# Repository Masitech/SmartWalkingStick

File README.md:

# SmartWalkingStick
Arduino ESP8266 based project to detect distance of object and alert it wireless to a bracelet that will vibrate and make sound

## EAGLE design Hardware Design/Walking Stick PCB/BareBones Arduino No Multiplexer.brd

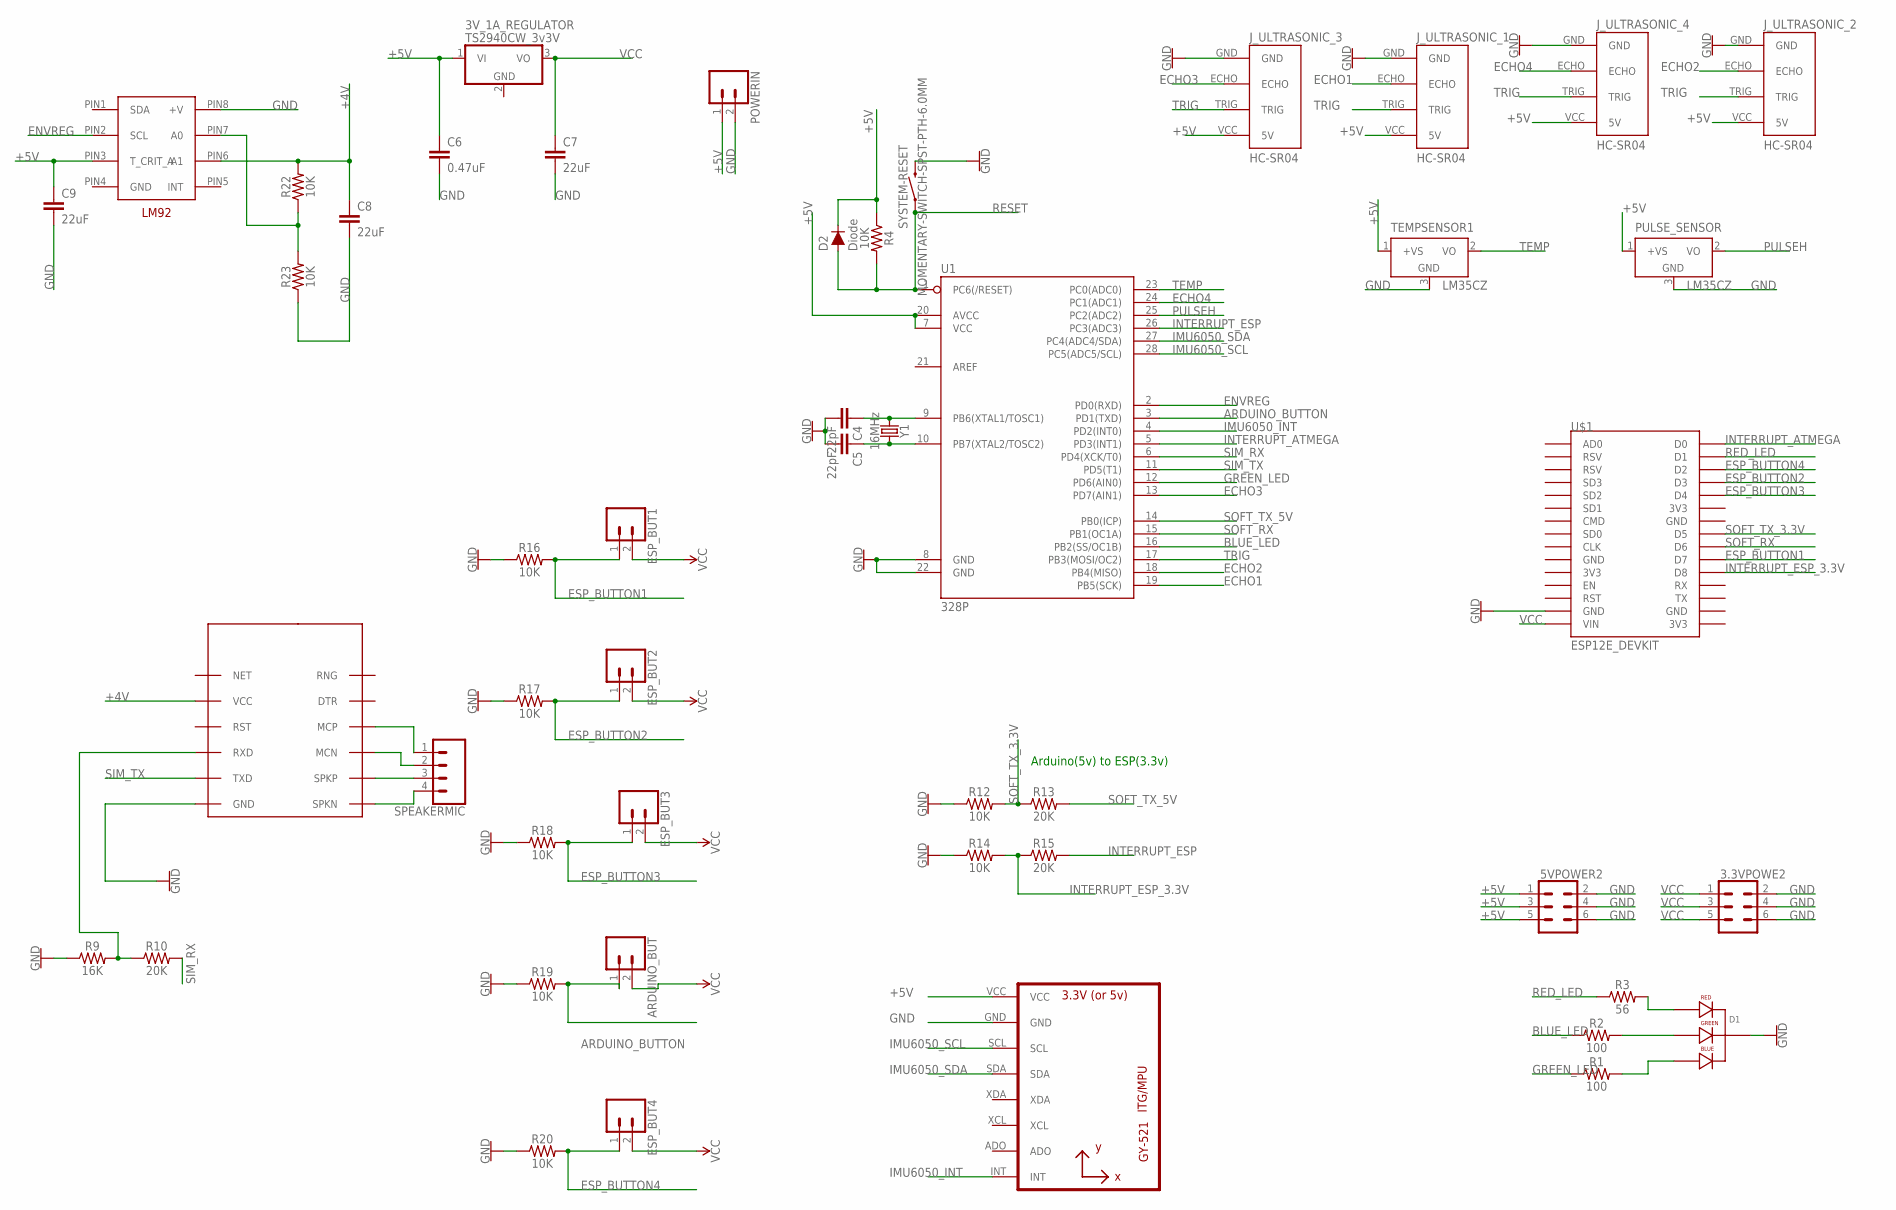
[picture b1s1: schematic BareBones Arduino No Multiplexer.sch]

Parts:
3.3VPOWE2, 5VPOWER2: CONN_03X2FEMALE; 2X3
3V_1A_REGULATOR: TS2940CW_3v3V; SOT223
ARDUINO_BUT: CONN_02; 1X02
C4, C5: 22pF; CAP-PTH-2.54
C6: 0.47uF; CAP-PTH-SMALL-KIT
C7, C8, C9: 22uF; CAP-PTH-SMALL-KIT
D1: LED-RGB-CC-THRUDIFFUSE; LED-RGB-THRU
D2: Diode; DIODE-1N4148
ESP_BUT1, ESP_BUT2, ESP_BUT3, ESP_BUT4: CONN_02; 1X02
J_ULTRASONIC_1, J_ULTRASONIC_2, J_ULTRASONIC_3, J_ULTRASONIC_4: HC-SR04; HC-SR04_FOOTPRINT
POWERIN: CONN_025MM; SCREWTERMINAL-5MM-2
PULSE_SENSOR: LM35CZ; TO92
R1, R2: 100; AXIAL-0.3
R3: 56; AXIAL-0.3
R4, R12, R14, R16, R17, R18, R19, R20, R22, R23: 10K; AXIAL-0.3
R9: 16K; AXIAL-0.3
R10, R13, R15: 20K; AXIAL-0.3
SPEAKERMIC: CONN_04; 1X04
SYSTEM-RESET: MOMENTARY-SWITCH-SPST-PTH-6.0MM; TACTILE_SWITCH_PTH_6.0MM
TEMPSENSOR1: LM35CZ; TO92
U1: 328P; DIP28
U2: GY-521MPU6050; GY-521
U$1: ESP12E_DEVKIT
U$4: SIM800L; SIM-CORE
VREG: LM92; SOP-8
Y1: 16MHz; HC49US

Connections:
+4V: C8.1, R22.P$2 (2), U$4.VCC, VREG.PIN6 (A1)
+5V: 3V_1A_REGULATOR.1 (VI), 5VPOWER2.1, 5VPOWER2.3, 5VPOWER2.5, C6.1, C9.1, D2.C, J_ULTRASONIC_1.VCC (5V), J_ULTRASONIC_2.VCC (5V), J_ULTRASONIC_3.VCC (5V), J_ULTRASONIC_4.VCC (5V), POWERIN.1, PULSE_SENSOR.1 (+VS), R4.P$1 (1), TEMPSENSOR1.1 (+VS), U1.7 (VCC), U1.20 (AVCC), U2.VCC, VREG.PIN3 (T_CRIT_A)
ARDUINO_BUTTON: ARDUINO_BUT.1, R19.P$2 (2), U1.3 (PD1(TXD))
BLUE_LED: R2.P$1 (1), U1.16 (PB2(SS/OC1B))
ECHO1: J_ULTRASONIC_1.ECHO, U1.19 (PB5(SCK))
ECHO2: J_ULTRASONIC_2.ECHO, U1.18 (PB4(MISO))
ECHO3: J_ULTRASONIC_3.ECHO, U1.13 (PD7(AIN1))
ECHO4: J_ULTRASONIC_4.ECHO, U1.24 (PC1(ADC1))
ENVREG: U1.2 (PD0(RXD)), VREG.PIN2 (SCL)
ESP_BUTTON1: ESP_BUT1.1, R16.P$2 (2), U$1.D7
ESP_BUTTON2: ESP_BUT2.1, R17.P$2 (2), U$1.D3
ESP_BUTTON3: ESP_BUT3.1, R18.P$2 (2), U$1.D4
ESP_BUTTON4: ESP_BUT4.1, R20.P$2 (2), U$1.D2
GND: 3.3VPOWE2.2, 3.3VPOWE2.4, 3.3VPOWE2.6, 5VPOWER2.2, 5VPOWER2.4, 5VPOWER2.6, C4.2, C5.2, C6.2, C7.2, C8.2, C9.2, D1.2 (CATHODE), J_ULTRASONIC_1.GND, J_ULTRASONIC_2.GND, J_ULTRASONIC_3.GND, J_ULTRASONIC_4.GND, POWERIN.2, PULSE_SENSOR.3 (GND), R9.P$1 (1), R12.P$1 (1), R14.P$1 (1), R16.P$1 (1), R17.P$1 (1), R18.P$1 (1), R19.P$1 (1), R20.P$1 (1), R23.P$1 (1), SYSTEM-RESET.3 (2), TEMPSENSOR1.3 (GND), U1.8 (GND), U1.22 (GND), U2.GND, U$1.GND@1 (GND), U$4.GND, VREG.PIN8 (+V)
GREEN_LED: R1.P$1 (1), U1.12 (PD6(AIN0))
IMU6050_INT: U1.4 (PD2(INT0)), U2.INT
IMU6050_SCL: U1.28 (PC5(ADC5/SCL)), U2.SCL
IMU6050_SDA: U1.27 (PC4(ADC4/SDA)), U2.SDA
INTERRUPT_ATMEGA: U1.5 (PD3(INT1)), U$1.D0
INTERRUPT_ESP: R15.P$2 (2), U1.26 (PC3(ADC3))
INTERRUPT_ESP_3.3V: R14.P$2 (2), R15.P$1 (1), U$1.D8
unnamed: C5.1, U1.10 (PB7(XTAL2/TOSC2)), Y1.2
unnamed: D1.1 (RED_CATHODE), R3.P$2 (2)
unnamed: D1.3 (GREEN_CATHODE), R2.P$2 (2)
unnamed: D1.4 (BLUE_CATHODE), R1.P$2 (2)
unnamed: SPEAKERMIC.1, U$4.MCP
unnamed: SPEAKERMIC.2, U$4.MCN
unnamed: C4.1, U1.9 (PB6(XTAL1/TOSC1)), Y1.1
unnamed: SPEAKERMIC.3, U$4.SPKP
unnamed: SPEAKERMIC.4, U$4.SPKN
unnamed: R9.P$2 (2), R10.P$1 (1), U$4.RXD
unnamed: R22.P$1 (1), R23.P$2 (2), VREG.PIN7 (A0)
PULSEH: PULSE_SENSOR.2 (VO), U1.25 (PC2(ADC2))
RED_LED: R3.P$1 (1), U$1.D1
RESET: D2.A, R4.P$2 (2), SYSTEM-RESET.1, U1.1 (PC6(/RESET))
SIM_RX: R10.P$2 (2), U1.6 (PD4(XCK/T0))
SIM_TX: U1.11 (PD5(T1)), U$4.TXD
SOFT_RX: U1.15 (PB1(OC1A)), U$1.D6
SOFT_TX_3.3V: R12.P$2 (2), R13.P$1 (1), U$1.D5
SOFT_TX_5V: R13.P$2 (2), U1.14 (PB0(ICP))
TEMP: TEMPSENSOR1.2 (VO), U1.23 (PC0(ADC0))
TRIG: J_ULTRASONIC_1.TRIG, J_ULTRASONIC_2.TRIG, J_ULTRASONIC_3.TRIG, J_ULTRASONIC_4.TRIG, U1.17 (PB3(MOSI/OC2))
VCC: 3.3VPOWE2.1, 3.3VPOWE2.3, 3.3VPOWE2.5, 3V_1A_REGULATOR.3 (VO), ARDUINO_BUT.2, C7.1, ESP_BUT1.2, ESP_BUT2.2, ESP_BUT3.2, ESP_BUT4.2, U$1.VIN

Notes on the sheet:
Arduino(5v) to ESP(3.3v)

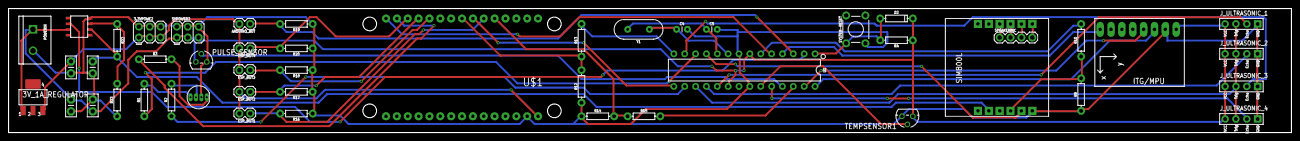
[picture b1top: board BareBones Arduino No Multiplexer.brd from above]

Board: 2 copper layers, 300.0 x 29.0 mm, 48 parts (0 on the bottom side), 43 nets.

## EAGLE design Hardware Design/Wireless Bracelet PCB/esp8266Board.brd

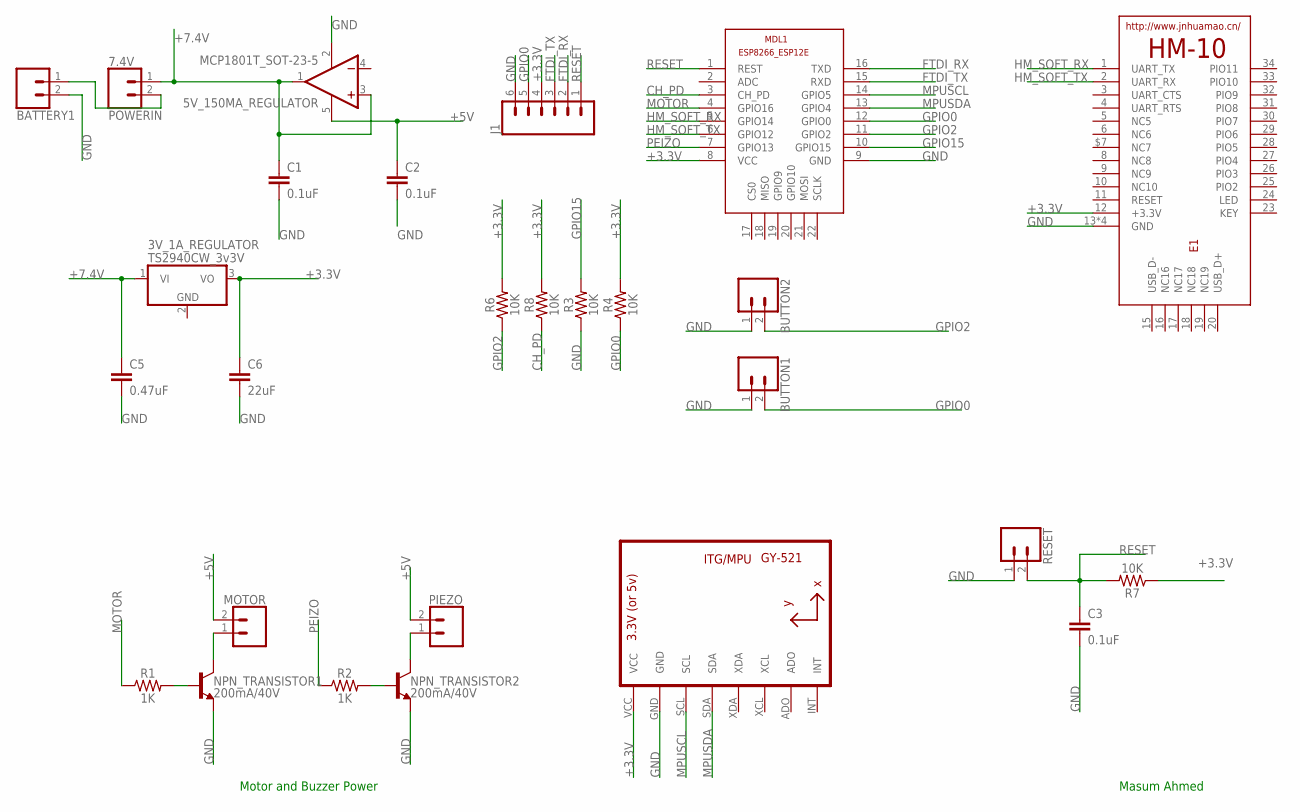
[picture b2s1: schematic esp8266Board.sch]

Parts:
3V_1A_REGULATOR: TS2940CW_3v3V; SOT223
5V_150MA_REGULATOR: MCP1801T_SOT-23-5; SOT23-5
BATTERY1: CONN_02; 1X02
BUTTON1, BUTTON2: CONN_02; 1X02
C1, C2, C3: 0.1uF; 0805
C5: 0.47uF; CAP-PTH-SMALL-KIT
C6: 22uF; CAP-PTH-SMALL-KIT
E1: HM-10-BOARD; 26.9X13X2.2_BOARD
J1: CONN_06SILK_FEMALE_PTH; 1X06
MDL1: ESP8266-12EESP8266-ESP12E; ESP8266-ESP12E
MOTOR: CONN_02; 1X02
NPN_TRANSISTOR1, NPN_TRANSISTOR2: 200mA/40V; TO-92
PIEZO: CONN_02; 1X02
POWERIN: 7.4V; 1X02
R1, R2: 1K; 0805
R3, R4, R6, R7, R8: 10K; 0805
RESET: CONN_02; 1X02
U1: GY-521MPU6050; GY-521

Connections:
+3.3V: 3V_1A_REGULATOR.3 (VO), C6.1, E1.12 (+3.3V), J1.4, MDL1.8 (VCC), R4.2, R6.2, R7.1, R8.2, U1.VCC
+5V: 5V_150MA_REGULATOR.5 (V+), C2.1, MOTOR.2, PIEZO.2
+7.4V: 3V_1A_REGULATOR.1 (VI), 5V_150MA_REGULATOR.1 (OUT), 5V_150MA_REGULATOR.3 (+IN), C1.1, C5.1, POWERIN.1
CH_PD: MDL1.3 (CH_PD), R8.1
FTDI_RX: J1.2, MDL1.16 (TXD)
FTDI_TX: J1.3, MDL1.15 (RXD)
GND: 5V_150MA_REGULATOR.2 (V-), BATTERY1.2, BUTTON1.1, BUTTON2.1, C1.2, C2.2, C3.2, C5.2, C6.2, E1.13 (GND), E1.14 (GND), E1.21 (GND), E1.22 (GND), J1.6, MDL1.9 (GND), NPN_TRANSISTOR1.1 (E), NPN_TRANSISTOR2.1 (E), R3.1, RESET.1, U1.GND
GPIO0: BUTTON1.2, J1.5, MDL1.12 (GPIO0), R4.1
GPIO2: BUTTON2.2, MDL1.11 (GPIO2), R6.1
GPIO15: MDL1.10 (GPIO15), R3.2
HM_SOFT_RX: E1.1 (UART_TX), MDL1.5 (GPIO14)
HM_SOFT_TX: E1.2 (UART_RX), MDL1.6 (GPIO12)
MOTOR: MDL1.4 (GPIO16), R1.1
MPUSCL: MDL1.14 (GPIO5), U1.SCL
MPUSDA: MDL1.13 (GPIO4), U1.SDA
unnamed: BATTERY1.1, POWERIN.2
unnamed: NPN_TRANSISTOR2.2 (B), R2.2
unnamed: NPN_TRANSISTOR1.2 (B), R1.2
unnamed: NPN_TRANSISTOR2.3 (C), PIEZO.1
unnamed: MOTOR.1, NPN_TRANSISTOR1.3 (C)
PEIZO: MDL1.7 (GPIO13), R2.1
RESET: C3.1, J1.1, MDL1.1 (REST), R7.2, RESET.2

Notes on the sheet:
Masum Ahmed
Motor and Buzzer Power

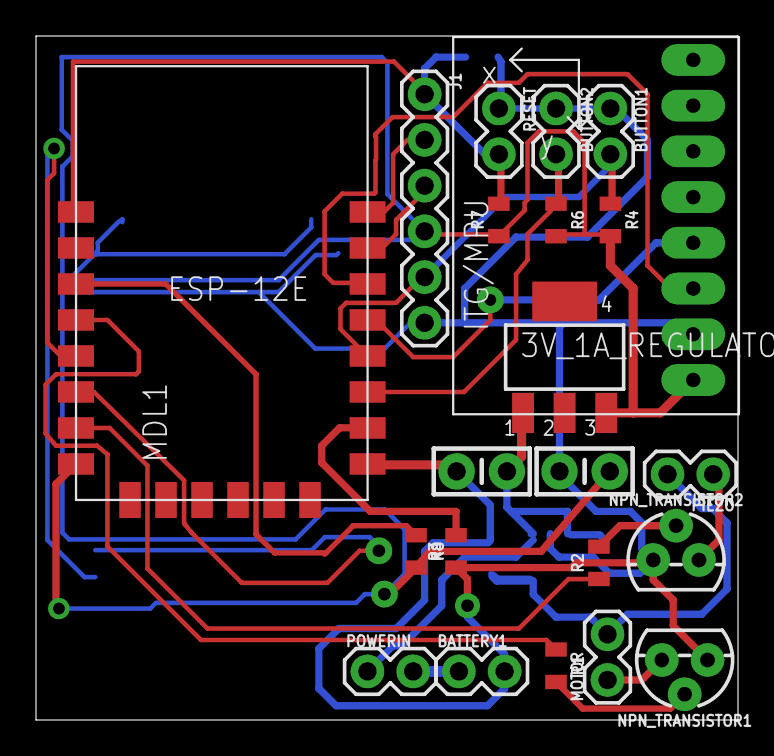
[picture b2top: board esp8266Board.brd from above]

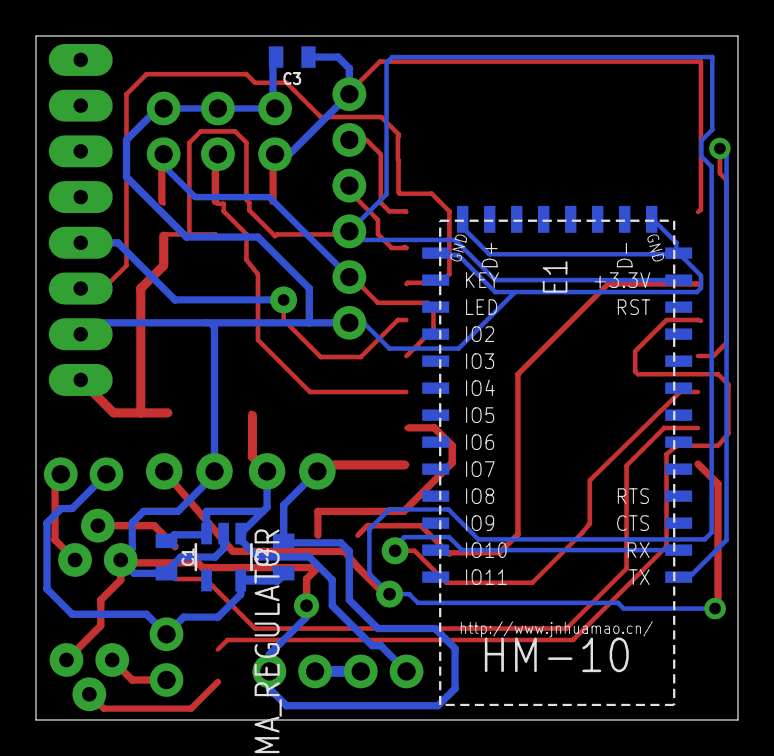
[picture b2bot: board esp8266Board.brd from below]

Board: 2 copper layers, 39.0 x 38.0 mm, 27 parts (5 on the bottom side), 22 nets.

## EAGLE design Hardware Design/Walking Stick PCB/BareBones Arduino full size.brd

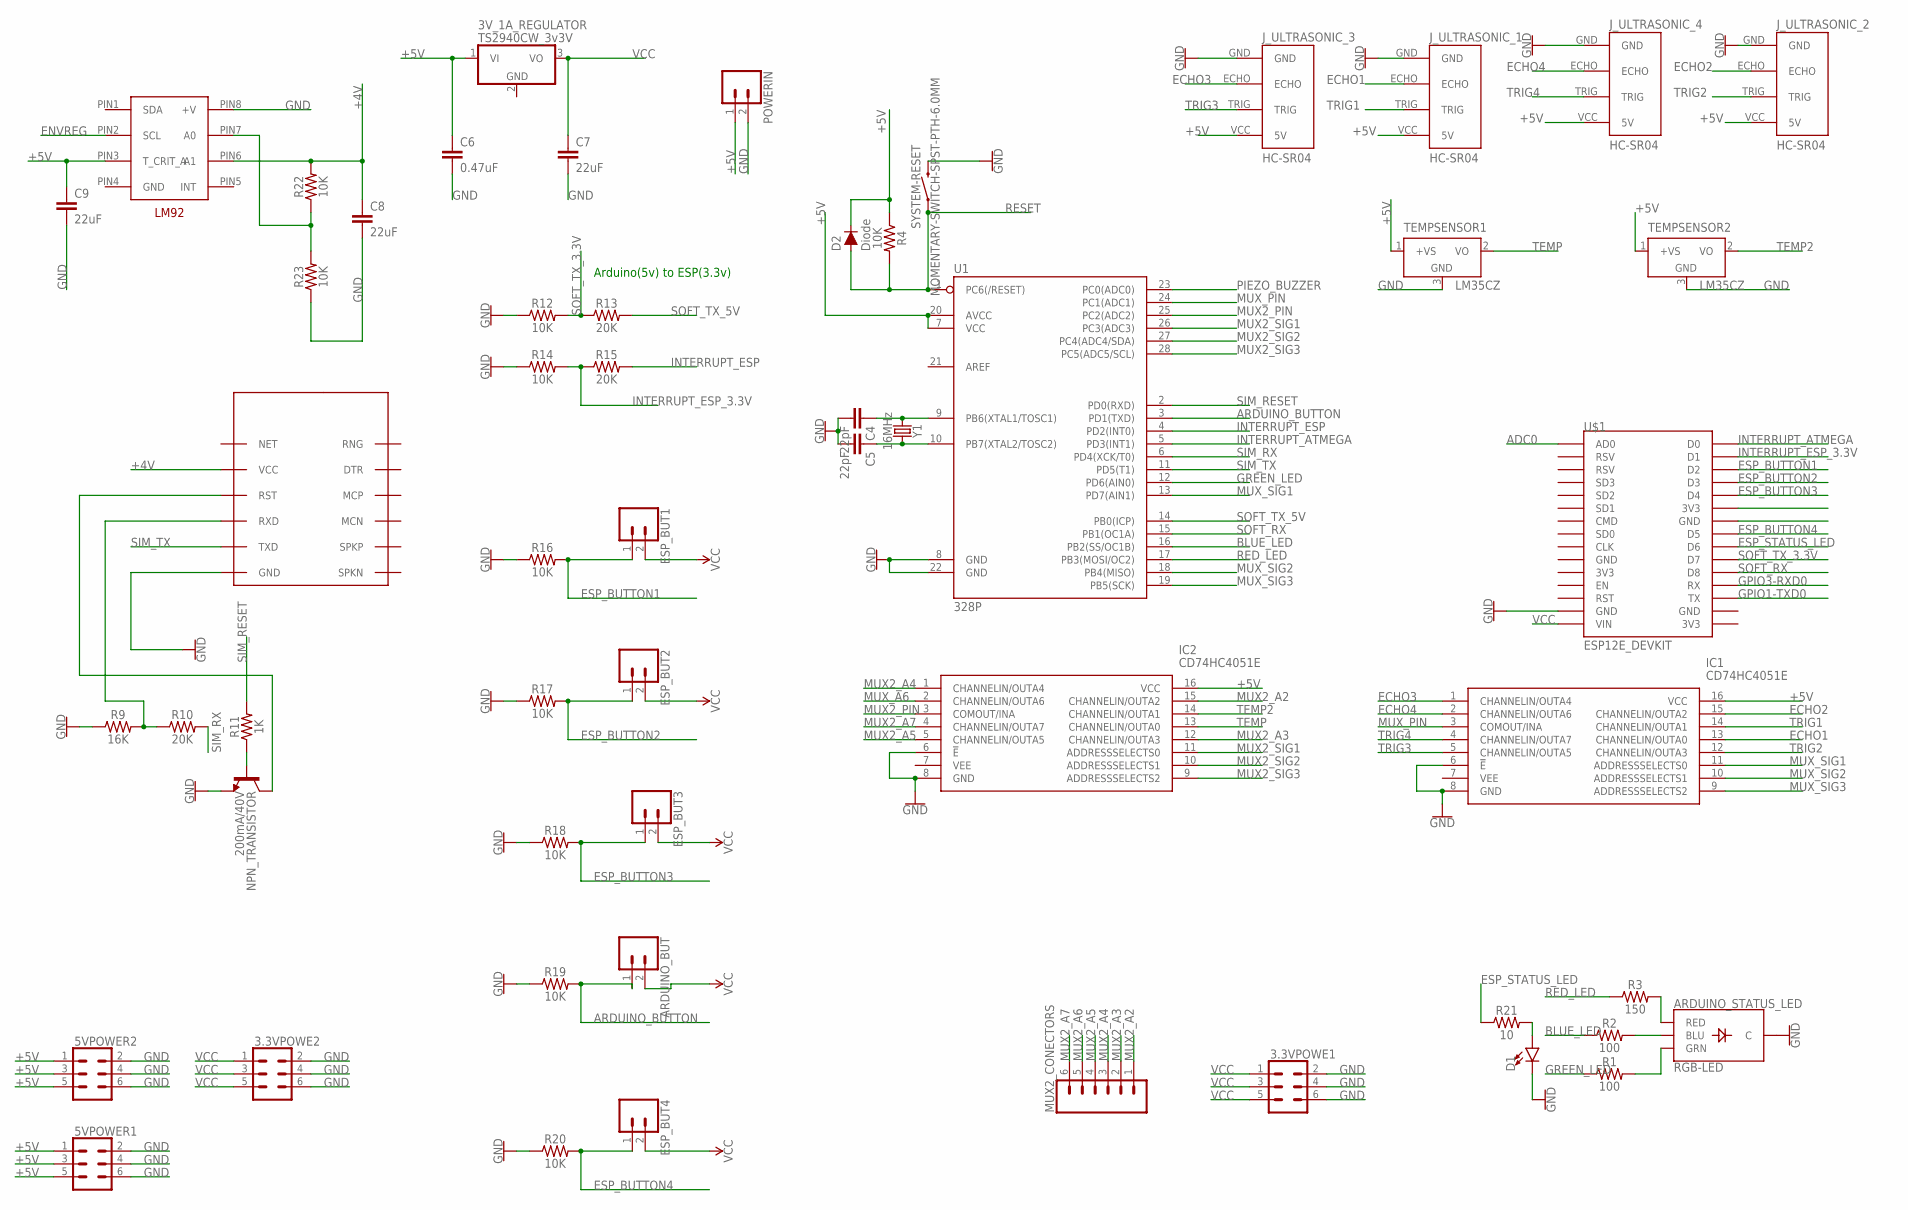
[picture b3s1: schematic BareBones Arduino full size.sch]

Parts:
3.3VPOWE1, 3.3VPOWE2, 5VPOWER1, 5VPOWER2: CONN_03X2FEMALE; 2X3
3V_1A_REGULATOR: TS2940CW_3v3V; SOT223
ARDUINO_BUT: CONN_02; 1X02
ARDUINO_STATUS_LED: RGB-LED; LED-RGB-THRU
C4, C5: 22pF; CAP-PTH-2.54
C6: 0.47uF; CAP-PTH-SMALL-KIT
C7, C8, C9: 22uF; CAP-PTH-SMALL-KIT
D1: LED5MM; LED_5MM
D2: Diode; DIODE-1N4148
ESP_BUT1, ESP_BUT2, ESP_BUT3, ESP_BUT4: CONN_02; 1X02
IC1, IC2: CD74HC4051E; DIP794W53P254L1930H508Q16N
J_ULTRASONIC_1, J_ULTRASONIC_2, J_ULTRASONIC_3, J_ULTRASONIC_4: HC-SR04; HC-SR04_FOOTPRINT
MUX2_CONECTORS: CONN_06SILK_FEMALE_PTH; 1X06
NPN_TRANSISTOR: 200mA/40V; TO-92
POWERIN: CONN_025MM; SCREWTERMINAL-5MM-2
R1, R2: 100; AXIAL-0.3
R3: 150; AXIAL-0.3
R4, R12, R14, R16, R17, R18, R19, R20, R22, R23: 10K; AXIAL-0.3
R9: 16K; AXIAL-0.3
R10, R13, R15: 20K; AXIAL-0.3
R11: 1K; AXIAL-0.3
R21: 10; AXIAL-0.3
SYSTEM-RESET: MOMENTARY-SWITCH-SPST-PTH-6.0MM; TACTILE_SWITCH_PTH_6.0MM
TEMPSENSOR1, TEMPSENSOR2: LM35CZ; TO92
U1: 328P; DIP28
U$1: ESP12E_DEVKIT
U$4: SIM800L; SIM-CORE
VREG: LM92; SOP-8
Y1: 16MHz; HC49US

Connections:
+4V: C8.1, R22.P$2 (2), U$4.VCC, VREG.PIN6 (A1)
+5V: 3V_1A_REGULATOR.1 (VI), 5VPOWER1.1, 5VPOWER1.3, 5VPOWER1.5, 5VPOWER2.1, 5VPOWER2.3, 5VPOWER2.5, C6.1, C9.1, D2.C, IC1.16 (VCC), IC2.16 (VCC), J_ULTRASONIC_1.VCC (5V), J_ULTRASONIC_2.VCC (5V), J_ULTRASONIC_3.VCC (5V), J_ULTRASONIC_4.VCC (5V), POWERIN.1, R4.P$1 (1), TEMPSENSOR1.1 (+VS), TEMPSENSOR2.1 (+VS), U1.7 (VCC), U1.20 (AVCC), VREG.PIN3 (T_CRIT_A)
ADC0: U$1.AD0
ARDUINO_BUTTON: ARDUINO_BUT.1, R19.P$2 (2), U1.3 (PD1(TXD))
BLUE_LED: R2.P$1 (1), U1.16 (PB2(SS/OC1B))
ECHO1: IC1.13 (CHANNELIN/OUTA0), J_ULTRASONIC_1.ECHO
ECHO2: IC1.15 (CHANNELIN/OUTA2), J_ULTRASONIC_2.ECHO
ECHO3: IC1.1 (CHANNELIN/OUTA4), J_ULTRASONIC_3.ECHO
ECHO4: IC1.2 (CHANNELIN/OUTA6), J_ULTRASONIC_4.ECHO
ENVREG: VREG.PIN2 (SCL)
ESP_BUTTON1: ESP_BUT1.1, R16.P$2 (2), U$1.D2
ESP_BUTTON2: ESP_BUT2.1, R17.P$2 (2), U$1.D3
ESP_BUTTON3: ESP_BUT3.1, R18.P$2 (2), U$1.D4
ESP_BUTTON4: ESP_BUT4.1, R20.P$2 (2), U$1.D5
ESP_STATUS_LED: R21.P$1 (1), U$1.D6
GND: 3.3VPOWE1.2, 3.3VPOWE1.4, 3.3VPOWE1.6, 3.3VPOWE2.2, 3.3VPOWE2.4, 3.3VPOWE2.6, 5VPOWER1.2, 5VPOWER1.4, 5VPOWER1.6, 5VPOWER2.2, 5VPOWER2.4, 5VPOWER2.6, ARDUINO_STATUS_LED.2 (C), C4.2, C5.2, C6.2, C7.2, C8.2, C9.2, D1.K (C), IC1.6 (!E), IC1.8 (GND), IC2.6 (!E), IC2.8 (GND), J_ULTRASONIC_1.GND, J_ULTRASONIC_2.GND, J_ULTRASONIC_3.GND, J_ULTRASONIC_4.GND, NPN_TRANSISTOR.1 (E), POWERIN.2, R9.P$1 (1), R12.P$1 (1), R14.P$1 (1), R16.P$1 (1), R17.P$1 (1), R18.P$1 (1), R19.P$1 (1), R20.P$1 (1), R23.P$1 (1), SYSTEM-RESET.3 (2), TEMPSENSOR1.3 (GND), TEMPSENSOR2.3 (GND), U1.8 (GND), U1.22 (GND), U$1.GND@1 (GND), U$4.GND, VREG.PIN8 (+V)
GPIO1-TXD0: U$1.TX
GPIO3-RXD0: U$1.RX
GREEN_LED: R1.P$1 (1), U1.12 (PD6(AIN0))
INTERRUPT_ATMEGA: U1.5 (PD3(INT1)), U$1.D0
INTERRUPT_ESP: R15.P$2 (2), U1.4 (PD2(INT0))
INTERRUPT_ESP_3.3V: R14.P$2 (2), R15.P$1 (1), U$1.D1
MUX2_A2: IC2.15 (CHANNELIN/OUTA2), MUX2_CONECTORS.1
MUX2_A3: IC2.12 (CHANNELIN/OUTA3), MUX2_CONECTORS.2
MUX2_A4: IC2.1 (CHANNELIN/OUTA4), MUX2_CONECTORS.3
MUX2_A5: IC2.5 (CHANNELIN/OUTA5), MUX2_CONECTORS.4
MUX2_A6: MUX2_CONECTORS.5
MUX2_A7: IC2.4 (CHANNELIN/OUTA7), MUX2_CONECTORS.6
MUX2_PIN: IC2.3 (COMOUT/INA), U1.25 (PC2(ADC2))
MUX2_SIG1: IC2.11 (ADDRESSSELECTS0), U1.26 (PC3(ADC3))
MUX2_SIG2: IC2.10 (ADDRESSSELECTS1), U1.27 (PC4(ADC4/SDA))
MUX2_SIG3: IC2.9 (ADDRESSSELECTS2), U1.28 (PC5(ADC5/SCL))
MUX_A6: IC2.2 (CHANNELIN/OUTA6)
MUX_PIN: IC1.3 (COMOUT/INA), U1.24 (PC1(ADC1))
MUX_SIG1: IC1.11 (ADDRESSSELECTS0), U1.13 (PD7(AIN1))
MUX_SIG2: IC1.10 (ADDRESSSELECTS1), U1.18 (PB4(MISO))
MUX_SIG3: IC1.9 (ADDRESSSELECTS2), U1.19 (PB5(SCK))
unnamed: C5.1, U1.10 (PB7(XTAL2/TOSC2)), Y1.2
unnamed: ARDUINO_STATUS_LED.1 (RED), R3.P$2 (2)
unnamed: ARDUINO_STATUS_LED.4 (BLU), R2.P$2 (2)
unnamed: ARDUINO_STATUS_LED.3 (GRN), R1.P$2 (2)
unnamed: C4.1, U1.9 (PB6(XTAL1/TOSC1)), Y1.1
unnamed: R9.P$2 (2), R10.P$1 (1), U$4.RXD
unnamed: NPN_TRANSISTOR.3 (C), U$4.RST
unnamed: D1.A, R21.P$2 (2)
unnamed: R22.P$1 (1), R23.P$2 (2), VREG.PIN7 (A0)
unnamed: NPN_TRANSISTOR.2 (B), R11.P$1 (1)
PIEZO_BUZZER: U1.23 (PC0(ADC0))
RED_LED: R3.P$1 (1), U1.17 (PB3(MOSI/OC2))
RESET: D2.A, R4.P$2 (2), SYSTEM-RESET.1, U1.1 (PC6(/RESET))
SIM_RESET: R11.P$2 (2), U1.2 (PD0(RXD))
SIM_RX: R10.P$2 (2), U1.6 (PD4(XCK/T0))
SIM_TX: U1.11 (PD5(T1)), U$4.TXD
SOFT_RX: U1.15 (PB1(OC1A)), U$1.D8
SOFT_TX_3.3V: R12.P$2 (2), R13.P$1 (1), U$1.D7
SOFT_TX_5V: R13.P$2 (2), U1.14 (PB0(ICP))
TEMP: IC2.13 (CHANNELIN/OUTA0), TEMPSENSOR1.2 (VO)
TEMP2: IC2.14 (CHANNELIN/OUTA1), TEMPSENSOR2.2 (VO)
TRIG1: IC1.14 (CHANNELIN/OUTA1), J_ULTRASONIC_1.TRIG
TRIG2: IC1.12 (CHANNELIN/OUTA3), J_ULTRASONIC_2.TRIG
TRIG3: IC1.5 (CHANNELIN/OUTA5), J_ULTRASONIC_3.TRIG
TRIG4: IC1.4 (CHANNELIN/OUTA7), J_ULTRASONIC_4.TRIG
VCC: 3.3VPOWE1.1, 3.3VPOWE1.3, 3.3VPOWE1.5, 3.3VPOWE2.1, 3.3VPOWE2.3, 3.3VPOWE2.5, 3V_1A_REGULATOR.3 (VO), ARDUINO_BUT.2, C7.1, ESP_BUT1.2, ESP_BUT2.2, ESP_BUT3.2, ESP_BUT4.2, U$1.VIN

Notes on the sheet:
Arduino(5v) to ESP(3.3v)

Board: 2 copper layers, 55 parts (0 on the bottom side), 56 nets, no tracks yet.

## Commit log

2020-06-28 removed sensitive info

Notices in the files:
parts and their libraries:
SparkFun-Connectors: Licensing: Creative Commons ShareAlike 4.0 International - https://creativecommons.org/licenses/by-sa/4.0
led: Licensing: CC v3.0 Share-Alike You are welcome to use this library for commercial purposes.
